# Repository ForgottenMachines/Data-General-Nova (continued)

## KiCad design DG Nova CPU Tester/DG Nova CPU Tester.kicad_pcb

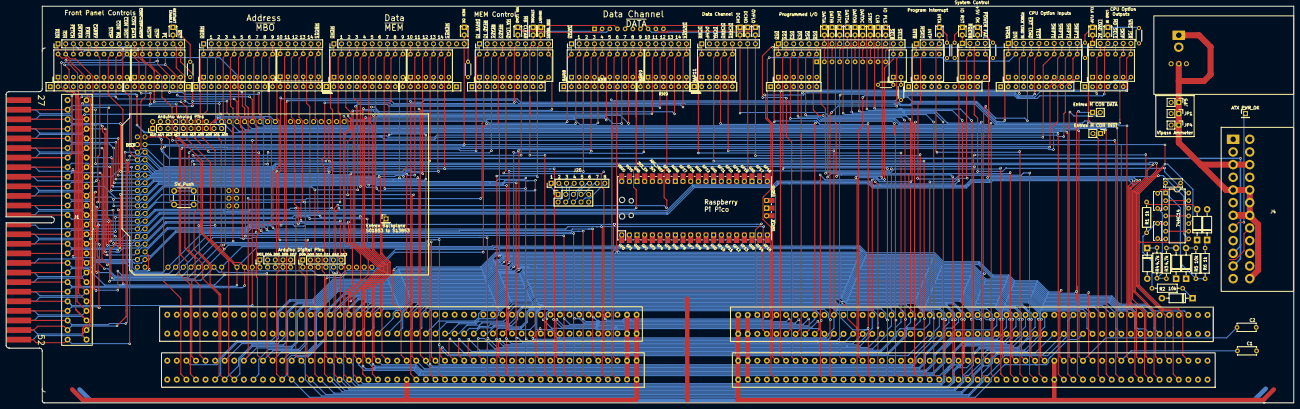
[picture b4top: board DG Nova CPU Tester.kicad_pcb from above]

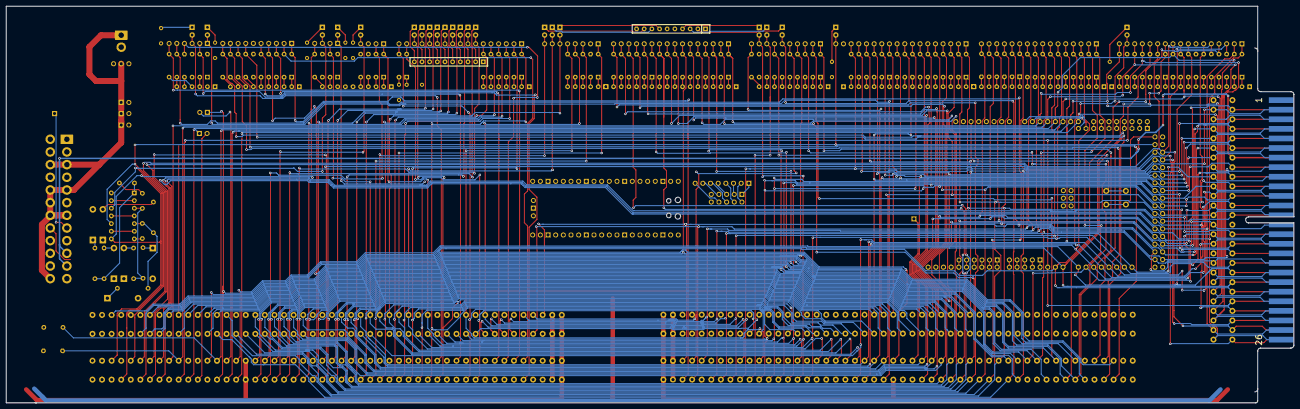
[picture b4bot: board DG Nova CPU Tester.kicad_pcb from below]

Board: 2 copper layers, 426.8 x 131.4 mm, 116 parts (2 on the bottom side), 303 nets.

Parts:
BAR1, BAR3, BAR5, BAR7, BAR8, BAR15: LED Bar 10
BAR2: LED Bar 10; LED Bar 7
BAR4, BAR6, BAR9, BAR10, BAR16: LED Bar 10; LED Bar 6
BAR11: LED Bar 10; LED Bar 5
BAR12: LED Bar 2
BAR13, BAR14: LED Bar 4
C1, C2: CAP_Disc_Common_-_Entrex_Trapezoid; Disc Capacitor Common Entrex Trapezoid
C3, C4, C5: C; C_Disc_D6.0mm_W2.5mm_P5.00mm
D1, D2, D3, D4, D5, D6: 1N4004; D_DO-41_SOD81_P10.16mm_Horizontal
D7, D8, D9, D10, D11, D12, D13, D14, D15, D16, D17, D18, D19, D20, D21, D22, D23, D24, D25, D26, D27, D28: LED; LED_D1.8mm_W3.3mm_H2.4mm
FPIMAGE1: MountingHole; nova frontpanel layout
J1: Front Panel Socket - Backside; DG NOVA Front Pannel Connector - Backside
J2, J3: DG NOVA Backplane Connector - Frontside
J4: ATX-24; Connector_2x12_P4.2mmx5.5mm (ATX Plug)
J5: Front Panel Card Edge; DG Nova Front Panel Card Edge
J6: MBO; PinHeader_1x16_P2.54mm_Vertical
J7: MEM; PinHeader_1x18_P2.54mm_Vertical
J8: Data Channel; PinHeader_1x16_P2.54mm_Vertical
J9: Front Panel Controls; PinHeader_1x17_P2.54mm_Vertical
J10: Programmed I/O; PinHeader_1x17_P2.54mm_Vertical
J11: CPU Option Inputs; PinHeader_1x10_P2.54mm_Vertical
J12: Data Channel; PinHeader_1x08_P2.54mm_Vertical
J13: Program Interrupt; PinHeader_1x04_P2.54mm_Vertical
J14: System Control; PinHeader_1x04_P2.54mm_Vertical
J15, J16: Slot_02x50_Odd_Even; DG NOVA Backplane Connector - Backside
J17: CPU Option Outputs; PinHeader_1x06_P2.54mm_Vertical
J18: MEM Control Outputs; PinHeader_1x10_P2.54mm_Vertical
J19: Logic 8 CH; PinHeader_2x05_P2.54mm_Vertical - Backside
J20: Logic 8 CH; PinHeader_1x08_P2.54mm_Vertical
J21: Arduino Anolog Pins; PinHeader_1x10_P2.54mm_Vertical
J22: Arduino Digital Pins; PinHeader_1x05_P2.54mm_Vertical
J23: Arduino Digital Pins; PinHeader_1x06_P2.54mm_Vertical
JP1, JP4, JP5: Vipass Ammeter; PinHeader_1x02_P2.54mm_Vertical
JP2: Entrex ~{M CON DATA}; PinHeader_1x02_P2.54mm_Vertical
JP3: Entrex ~{M CON INST}; PinHeader_1x02_P2.54mm_Vertical
MES1: XK-001; XK-001_Volt-Amp_Meter - Backside
R1, R6: 1k; R_Axial_DIN0207_L6.3mm_D2.5mm_P10.16mm_Horizontal
R2, R5: 10k; R_Axial_DIN0207_L6.3mm_D2.5mm_P10.16mm_Horizontal
R3, R4: 4.7k; R_Axial_DIN0207_L6.3mm_D2.5mm_P10.16mm_Horizontal
R7, R8, R9, R10, R11, R12, R13, R14, R15: R_US; R_Axial_DIN0204_L3.6mm_D1.6mm_P5.08mm_Horizontal
RN1, RN3, RN5, RN7, RN8, RN11, RN13, RN14, RN15: R_Network09_US; R_Array_SIP10
RN2: R_Network08_US; R_Array_SIP9
RN4, RN6, RN9: R_Network07_US; R_Array_SIP8
RN10, RN16: R_Network05_US; R_Array_SIP6
RN12: R_Network06_US; R_Array_SIP7
SW1: SW_Push; SW_PUSH_6mm
TP1: Entrex Backplane S01B53 to S13B53; PinHeader_1x01_P2.54mm_Vertical
TP2: ATX PWR_OK; PinHeader_1x01_P2.54mm_Vertical
U1: 74HC14; DIP-14_W7.62mm
U2: Pico; RPi_Pico_SMD_TH
XA1: Arduino_Mega2560_Shield

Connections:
+3v3: J4.1 (+3.3V), J4.2 (+3.3V), J4.12 (+3.3V), J4.13 (+3.3V)
+5V: D1.1 (K), D2.2 (A), D3.1 (K), D4.2 (A), D5.1 (K), D6.2 (A), J1.27, J2.3, J2.4, J2.97, J2.98, J3.3, J3.4, J3.97, J3.98, J4.4 (+5V), J4.6 (+5V), J4.21 (+5V), J4.22 (+5V), J4.23 (+5V), J5.27, J15.3, J15.4, J15.97 (Pin_69), J15.98, J16.3, J16.4, J16.97 (Pin_69), J16.98, MES1.1, MES1.3 (PWR), R9.1, R10.1, RN1.1 (common), RN2.1 (common), RN3.1 (common), RN4.1 (common), RN5.1 (common), RN6.1 (common), RN7.1 (common), RN8.1 (common), RN9.1 (common), RN10.1 (common), RN12.1 (common), RN13.1 (common), RN15.1 (common), RN16.1 (common), U1.14 (VCC), U2.39 (VSYS), XA1.5V1 (5V), XA1.5V3 (5V), XA1.5V4 (5V), XA1.VIN
+5V OK: D24.2 (A), J2.8, J14.3, U1.12
+12V Lamp: J1.33, J4.10 (+12V), J4.11 (+12V), J5.33
+VINH: J15.10, J16.84
-5V: J4.20 (-5v), J15.6, J16.81
CLK FLOP: D28.2 (A), J3.48, J17.1
CLR: D20.2 (A), J2.50, J10.14, J15.50
DATIA: D12.2 (A), J2.44, J10.7, J15.44
DATIB: D16.2 (A), J2.42, J10.8, J15.42
DATIC: D17.2 (A), J2.54, J10.9, J15.54
DATOA: D21.2 (A), J2.58, J10.10, J15.58
DATOB: D22.2 (A), J2.56, J10.11, J15.56
DATOC: D18.2 (A), J2.48, J10.12, J15.48
DCHI: D13.2 (A), J3.37, J12.6, J16.37
DCHO: D14.2 (A), J3.33, J12.7, J16.33
Entrex Backplane S01B53 to S13B53: J3.53, TP1.1
Entrex P10.19: J2.24, JP3.2 (B)
Entrex P10.30: J2.29, JP2.2 (B)
GND: C1.1, C2.1, C3.2, C4.2, C5.2, J1.1, J1.40, J2.1, J2.2, J2.33, J2.34, J2.99, J2.100, J3.1, J3.2, J3.50, J3.99, J3.100, J5.1, J5.40, J15.1, J15.2, J15.33, J15.34, J15.99, J15.100, J16.1, J16.2, J16.50, J16.89, J16.92, J16.99, J16.100, J19.10, JP1.2 (B), JP4.2 (B), JP5.2 (B), MES1.5, R7.1, R8.1, R11.1, R12.1, R13.1, R14.1, R15.1, RN11.1 (common), RN14.1 (common), SW1.1, U1.7 (GND), U2.3 (GND), U2.8 (GND), U2.13 (GND), U2.18 (GND), U2.23 (GND), U2.28 (GND), U2.33 (AGND), U2.38 (GND), U2.42 (GND), XA1.GND1 (GND), XA1.GND2 (GND), XA1.GND3 (GND), XA1.GND5 (GND), XA1.GND6 (GND)
GND After Meter: J4.3 (GND), J4.5 (GND), J4.7 (GND), J4.15 (GND), J4.17 (GND), J4.18 (GND), J4.19 (GND), J4.24 (GND), JP1.1 (A), JP4.1 (A), JP5.1 (A), MES1.2, MES1.4
INH GND: J15.8, J15.14, J15.16, J15.20, J15.22, J15.26, J15.30, J15.31
INHIBIT: D11.2 (A), J3.30, J16.30, J18.9
INTA: D25.2 (A), J2.40, J13.4, J15.40
IO PLS: D23.2 (A), J2.74, J10.15, J15.74
IO RST: D26.2 (A), J2.70, J14.1, J15.70
LOAD IR: D27.2 (A), J2.73, J17.3
Logic1: J19.1, J20.1
Logic2: J19.2, J20.2
Logic3: J19.3, J20.3
Logic4: J19.4, J20.4
Logic5: J19.5, J20.5
Logic6: J19.6, J20.6
Logic7: J19.7, J20.7
Logic8: J19.8, J20.8
MB LOAD: D9.2 (A), J3.74, J16.74, J18.6
MEM OK: D8.2 (A), J2.9, J7.18, U1.10, XA1.D52
unnamed: BAR12.1, R10.2
unnamed: BAR12.2, R9.2
unnamed: C3.1, R1.2, R2.1, U1.5
unnamed: C4.1, R3.2, R4.1, U1.3
unnamed: C5.1, R5.2, R6.1, U1.1
unnamed: D1.2 (A), R1.1
unnamed: D2.1 (K), R2.2
unnamed: D3.2 (A), R3.1
unnamed: D4.1 (K), R4.2
unnamed: D5.2 (A), R5.1
unnamed: D6.1 (K), R6.2
unnamed: D7.1 (K), R7.2
unnamed: D8.1 (K), R8.2
unnamed: D9.1 (K), RN11.2 (R1)
unnamed: D10.1 (K), RN11.3 (R2)
unnamed: D11.1 (K), RN11.4 (R3)
unnamed: D12.1 (K), RN14.2 (R1)
unnamed: D13.1 (K), RN11.7 (R6)
unnamed: D14.1 (K), RN11.8 (R7)
unnamed: D15.1 (K), RN11.9 (R8)
unnamed: D16.1 (K), RN14.3 (R2)
unnamed: D17.1 (K), RN14.4 (R3)
unnamed: D18.1 (K), RN14.7 (R6)
unnamed: D19.1 (K), RN14.8 (R7)
unnamed: D20.1 (K), RN14.9 (R8)
unnamed: D21.1 (K), RN14.5 (R4)
unnamed: D22.1 (K), RN14.6 (R5)
unnamed: D23.1 (K), RN14.10 (R9)
unnamed: D24.1 (K), R14.2
unnamed: D25.1 (K), R11.2
unnamed: D26.1 (K), R12.2
unnamed: D27.1 (K), R13.2
unnamed: D28.1 (K), R15.2
unnamed: J21.1, XA1.A15
unnamed: J21.2, XA1.A14
unnamed: J21.3, XA1.A13
unnamed: J21.4, XA1.A12
unnamed: J21.5, XA1.A11
unnamed: J21.6, XA1.A10
unnamed: J21.7, XA1.A9
unnamed: J21.8, XA1.A8
unnamed: J21.9, XA1.A1
unnamed: J21.10, XA1.A0
unnamed: J22.1, XA1.D3 (D3_INT1)
unnamed: J22.2, XA1.D4
unnamed: J22.3, XA1.D5
unnamed: J22.4, XA1.D6
unnamed: J22.5, XA1.D7
unnamed: J23.1, XA1.D8
unnamed: J23.2, XA1.D9
unnamed: J23.3, XA1.D10
unnamed: J23.4, XA1.D11
unnamed: J23.5, XA1.D12
unnamed: J23.6, XA1.D13
unnamed: BAR1.1, RN1.2 (R1)
unnamed: BAR1.2, RN1.3 (R2)
unnamed: BAR1.3, RN1.4 (R3)
unnamed: BAR1.4, RN1.5 (R4)
unnamed: BAR1.5, RN1.6 (R5)
unnamed: BAR1.6, RN1.7 (R6)
unnamed: BAR1.7, RN1.8 (R7)
unnamed: BAR1.8, RN1.9 (R8)
unnamed: BAR1.9, RN1.10 (R9)
unnamed: BAR2.7, RN2.2 (R1)
unnamed: BAR2.6, RN2.3 (R2)
unnamed: BAR2.5, RN2.4 (R3)
unnamed: BAR2.4, RN2.5 (R4)
unnamed: BAR2.3, RN2.6 (R5)
unnamed: BAR2.2, RN2.7 (R6)
unnamed: BAR2.1, RN2.8 (R7)
unnamed: BAR1.10, RN2.9 (R8)
unnamed: BAR3.1, RN3.2 (R1)
unnamed: BAR3.2, RN3.3 (R2)
unnamed: BAR3.3, RN3.4 (R3)
unnamed: BAR3.4, RN3.5 (R4)
unnamed: BAR3.5, RN3.6 (R5)
unnamed: BAR3.6, RN3.7 (R6)
unnamed: BAR3.7, RN3.8 (R7)
unnamed: BAR3.8, RN3.9 (R8)
unnamed: BAR3.9, RN3.10 (R9)
unnamed: BAR4.6, RN4.2 (R1)
unnamed: BAR4.5, RN4.3 (R2)
unnamed: BAR4.4, RN4.4 (R3)
unnamed: BAR4.3, RN4.5 (R4)
unnamed: BAR4.2, RN4.6 (R5)
unnamed: BAR4.1, RN4.7 (R6)
unnamed: BAR3.10, RN4.8 (R7)
unnamed: BAR5.1, RN5.2 (R1)
unnamed: BAR5.2, RN5.3 (R2)
unnamed: BAR5.3, RN5.4 (R3)
unnamed: BAR5.4, RN5.5 (R4)
unnamed: BAR5.5, RN5.6 (R5)
unnamed: BAR5.6, RN5.7 (R6)
unnamed: BAR5.7, RN5.8 (R7)
unnamed: BAR5.8, RN5.9 (R8)
unnamed: BAR5.9, RN5.10 (R9)
unnamed: BAR6.6, RN6.2 (R1)
unnamed: BAR6.5, RN6.3 (R2)
unnamed: BAR6.4, RN6.4 (R3)
unnamed: BAR6.3, RN6.5 (R4)
unnamed: BAR6.2, RN6.6 (R5)
unnamed: BAR6.1, RN6.7 (R6)
unnamed: BAR5.10, RN6.8 (R7)
unnamed: BAR7.1, RN7.2 (R1)
unnamed: BAR7.2, RN7.3 (R2)
unnamed: BAR7.3, RN7.4 (R3)
unnamed: BAR7.4, RN7.5 (R4)
unnamed: BAR7.5, RN7.6 (R5)
unnamed: BAR7.6, RN7.7 (R6)
unnamed: BAR7.7, RN7.8 (R7)
unnamed: BAR7.8, RN7.9 (R8)
unnamed: BAR7.10, RN7.10 (R9)
unnamed: BAR8.1, RN8.2 (R1)
unnamed: BAR8.2, RN8.3 (R2)
unnamed: BAR8.3, RN8.4 (R3)
unnamed: BAR8.4, RN8.5 (R4)
unnamed: BAR8.5, RN8.6 (R5)
unnamed: BAR8.6, RN8.7 (R6)
unnamed: BAR8.7, RN8.8 (R7)
unnamed: BAR8.8, RN8.9 (R8)
unnamed: BAR8.9, RN8.10 (R9)
unnamed: BAR9.6, RN9.2 (R1)
unnamed: BAR9.5, RN9.3 (R2)
unnamed: BAR9.4, RN9.4 (R3)
unnamed: BAR9.3, RN9.5 (R4)
unnamed: BAR9.2, RN9.6 (R5)
unnamed: BAR9.1, RN9.7 (R6)
unnamed: BAR8.10, RN9.8 (R7)
unnamed: BAR11.1, RN10.2 (R1)
unnamed: BAR11.2, RN10.3 (R2)
unnamed: BAR11.3, RN10.4 (R3)
unnamed: BAR11.4, RN10.5 (R4)
unnamed: BAR11.5, RN10.6 (R5)
unnamed: BAR10.1, RN12.2 (R1)
unnamed: BAR10.2, RN12.3 (R2)
unnamed: BAR10.3, RN12.4 (R3)
unnamed: BAR10.4, RN12.5 (R4)
unnamed: BAR10.5, RN12.6 (R5)
unnamed: BAR10.6, RN12.7 (R6)
unnamed: BAR13.1, RN13.2 (R1)
unnamed: BAR13.2, RN13.3 (R2)
unnamed: BAR13.3, RN13.4 (R3)
unnamed: BAR13.4, RN13.5 (R4)
unnamed: BAR14.2, RN13.9 (R8)
unnamed: BAR14.4, RN13.10 (R9)
unnamed: BAR15.1, RN15.2 (R1)
unnamed: BAR15.2, RN15.3 (R2)
unnamed: BAR15.3, RN15.4 (R3)
unnamed: BAR15.4, RN15.5 (R4)
unnamed: BAR15.5, RN15.6 (R5)
unnamed: BAR15.7, RN15.7 (R6)
unnamed: BAR15.8, RN15.8 (R7)
unnamed: BAR15.9, RN15.9 (R8)
unnamed: BAR15.10, RN15.10 (R9)
unnamed: BAR16.2, RN16.3 (R2)
unnamed: BAR16.6, RN16.4 (R3)
unnamed: BAR16.4, RN16.5 (R4)
unnamed: BAR16.5, RN16.6 (R5)
unnamed: U1.6, U1.9
unnamed: U1.4, U1.11
unnamed: U1.2, U1.13
unnamed: SW1.2, XA1.RST1 (RESET)
OVFLO: D15.2 (A), J3.39, J12.8, J16.39
PWR_OK: J4.8 (PWR_OK), TP2.1
RESTART ENABLE: D7.2 (A), J1.19, J2.32, J5.19, J9.16, XA1.A7
STROBE: D10.2 (A), J3.20, J16.20, J18.8
STRT: D19.2 (A), J2.52, J10.13, J15.52
~CARRY: BAR1.15 (K), J1.49, J2.15, J5.49, J9.6, XA1.D32
~CON DATA: BAR2.20 (K), J1.46, J2.28, J5.46, J9.11, JP2.1 (A), XA1.D0 (D0_RX0)
~CON INST: BAR1.11 (K), J1.22, J2.22, J5.22, J9.10, JP3.1 (A), XA1.A4
~CON RQ: BAR1.12 (K), C2.2, J1.21, J2.27, J5.21, J9.9, XA1.A5
~CONT+ISTP+MSTP: BAR2.19 (K), J1.47, J2.25, J5.47, J9.12, XA1.D1 (D1_TX0)
~DATA0: BAR8.20 (K), J3.62, J8.1, J16.62
~DATA1: BAR8.19 (K), J3.65, J8.2, J16.65
~DATA2: BAR8.18 (K), J3.82, J8.3, J16.82
~DATA3: BAR8.17 (K), J3.73, J8.4, J16.73
~DATA4: BAR8.16 (K), J3.61, J8.5, J16.61
~DATA5: BAR8.15 (K), J3.57, J8.6, J16.57
~DATA6: BAR8.14 (K), J3.95, J8.7, J16.95
~DATA7: BAR8.13 (K), J3.55, J8.8, J16.55
~DATA8: BAR8.12 (K), J3.60, J8.9, J16.60
~DATA9: BAR8.11 (K), J3.63, J8.10, J16.63
~DATA10: BAR9.20 (K), J3.75, J8.11, J16.75
~DATA11: BAR9.19 (K), J3.58, J8.12, J16.58
~DATA12: BAR9.18 (K), J3.59, J8.13, J16.59
~DATA13: BAR9.17 (K), J3.64, J8.14, J16.64
~DATA14: BAR9.16 (K), J3.56, J8.15, J16.56
~DATA15: BAR9.15 (K), J3.66, J8.16, J16.66
~DCHA: BAR11.18 (K), J2.60, J12.3, J15.60
~DCHM0: BAR11.17 (K), J3.17, J12.4, J16.17
~DCHM1: BAR11.16 (K), J3.21, J12.5, J16.21
~DCHR: BAR11.20 (K), J3.35, J12.1, J16.35
~DEFER: BAR1.17 (K), J1.52, J2.12, J5.52, J9.4, XA1.D50
~DIV: BAR15.19 (K), J2.91, J11.2
~DRIVE IO: BAR7.20 (K), J3.88, J16.88, J18.1
~DS0: BAR10.20 (K), J2.72, J10.1, J15.72
~DS1: BAR10.19 (K), J2.68, J10.2, J15.68
~DS2: BAR10.18 (K), J2.66, J10.3, J15.66
~DS3: BAR10.17 (K), J2.46, J10.4, J15.46
~DS4: BAR10.16 (K), J2.62, J10.5, J15.62
~DS5: BAR10.15 (K), J2.64, J10.6, J15.64
~EXEC: BAR1.16 (K), J1.51, J2.11, J5.51, J9.5, XA1.D51
~EXT LOAD: BAR15.17 (K), J2.47, J3.49, J11.4
~FETCH: BAR1.18 (K), J1.50, J2.13, J2.49, J5.50, J9.3, XA1.D49
~FORCE LOAD IR: BAR15.18 (K), J2.85, J11.3
~INH TRANS: BAR7.11 (K), J3.45, J16.45, J18.10
~INTR: BAR13.20 (K), J3.29, J13.1, J16.29
~ION: BAR1.19 (K), J1.25, J2.16, J5.25, J9.2, XA1.D31
~ISTP: BAR2.17 (K), J1.24, J2.17, J5.24, J9.14, XA1.A2
~LOAD AC: BAR16.19 (K), J2.77, J17.2
~MA LOAD: BAR7.16 (K), J3.7, J16.7, J18.5
~MB CLEAR: BAR7.14 (K), J3.86, J16.86, J18.7
~MBO0: BAR3.20 (K), J3.79, J6.1, J16.79
~MBO1: BAR3.19 (K), J1.14, J3.77, J5.14, J6.2, J16.77, XA1.D15 (D15_RX3)
~MBO2: BAR3.18 (K), J1.15, J3.44, J5.15, J6.3, J16.44, XA1.D16 (D16_TX2)
~MBO3: BAR3.17 (K), J1.38, J3.43, J5.38, J6.4, J16.43, XA1.D17 (D17_RX2)
~MBO4: BAR3.16 (K), J1.16, J3.42, J5.16, J6.5, J16.42, XA1.D18 (D18_TX1)
~MBO5: BAR3.15 (K), J1.11, J3.32, J5.11, J6.6, J16.32, XA1.D19 (D19_RX1)
~MBO6: BAR3.14 (K), J1.35, J3.16, J5.35, J6.7, J16.16, XA1.D20 (D20_SDA)
~MBO7: BAR3.13 (K), J1.9, J3.14, J5.9, J6.8, J16.14, XA1.D21 (D21_SCL)
~MBO8: BAR3.12 (K), J1.18, J3.12, J5.18, J6.9, J16.12, XA1.D22
~MBO9: BAR3.11 (K), J1.8, J3.9, J5.8, J6.10, J16.9, XA1.D23
~MBO10: BAR4.20 (K), J1.44, J3.8, J5.44, J6.11, J16.8, XA1.D24
~MBO11: BAR4.19 (K), J1.6, J3.5, J5.6, J6.12, J16.5, XA1.D25
~MBO12: BAR4.18 (K), J1.30, J2.39, J5.30, J6.13, J15.39, XA1.D26
~MBO13: BAR4.17 (K), J1.4, J2.37, J5.4, J6.14, J15.37, XA1.D27
~MBO14: BAR4.16 (K), J1.12, J2.43, J5.12, J6.15, J15.43, XA1.D28
~MBO15: BAR4.15 (K), J1.28, J2.41, J5.28, J6.16, J15.41, XA1.D29
~MD SEL1: BAR16.17 (K), J2.87, J17.4
~MEM0: BAR5.20 (K), J1.39, J3.71, J5.39, J7.1, J16.71, XA1.D33
~MEM1: BAR5.19 (K), J1.41, J3.70, J5.41, J7.2, J16.70, XA1.D34
~MEM2: BAR5.18 (K), J1.13, J3.47, J5.13, J7.3, J16.47, XA1.D35
~MEM3: BAR5.17 (K), J1.43, J3.68, J5.43, J7.4, J16.68, XA1.D36
~MEM4: BAR5.16 (K), J1.37, J3.28, J5.37, J7.5, J16.28, XA1.D37
~MEM5: BAR5.15 (K), J1.36, J3.26, J5.36, J7.6, J16.26, XA1.D38
~MEM6: BAR5.14 (K), J1.10, J3.22, J5.10, J7.7, J16.22, XA1.D39
~MEM7: BAR5.13 (K), J1.42, J3.24, J5.42, J7.8, J16.24, XA1.D40
~MEM8: BAR5.12 (K), J1.34, J2.55, J5.34, J7.9, J15.55, XA1.D41
~MEM9: BAR5.11 (K), J1.7, J2.53, J5.7, J7.10, J15.53, XA1.D42
~MEM10: BAR6.20 (K), J1.32, J2.45, J5.32, J7.11, J15.45, XA1.D43
~MEM11: BAR6.19 (K), J1.31, J2.51, J5.31, J7.12, J15.51, XA1.D44
~MEM12: BAR6.18 (K), J1.5, J2.36, J5.5, J7.13, J15.36, XA1.D45
~MEM13: BAR6.17 (K), J1.29, J2.35, J5.29, J7.14, J15.35, XA1.D46
~MEM14: BAR6.16 (K), J1.3, J3.76, J5.3, J7.15, J16.76, XA1.D47
~MEM15: BAR6.15 (K), J1.2, J3.18, J5.2, J7.16, J16.18, XA1.D48
~MSKO: BAR13.19 (K), J2.38, J13.2, J15.38
~MSTP: BAR2.18 (K), J1.48, J2.20, J5.48, J9.13, XA1.D2 (D2_INT0)
~PL: BAR2.16 (K), C1.2, J1.23, J2.19, J5.23, J9.15, XA1.A3
~POWER FAIL: BAR14.17 (K), J2.5, J14.4, U1.8
~READ1: BAR7.18 (K), J3.87, J16.87, J18.3
~READ2: BAR7.17 (K), J3.90, J16.90, J18.4
~READ IO: BAR7.19 (K), J3.83, J16.83, J18.2
~RQENB: BAR14.19 (K), J3.41, J14.2, J16.41
~RST: BAR2.14 (K), J1.20, J2.30, J5.20, J9.17, XA1.A6
~RUN: BAR1.20 (K), J1.26, J2.14, J5.26, J9.1, XA1.D30
~SELB: BAR12.20 (K), J2.82, J10.16, J15.82
~SELD: BAR12.19 (K), J2.80, J10.17, J15.80
~SHIFT0: BAR15.14 (K), J3.94, J11.7
~SHIFT1: BAR15.13 (K), J3.96, J11.8
~SHIFT2: BAR15.12 (K), J3.93, J11.9
~SHIFT3: BAR15.11 (K), J3.91, J11.10
~SKIP: BAR16.16 (K), J3.69, J17.5
~STOP: BAR1.13 (K), J1.45, J2.31, J5.45, J9.8, XA1.D14 (D14_TX3)
~TEST: BAR15.16 (K), J2.92, J11.5
~WAS JSR: BAR16.15 (K), J2.89, J17.6
~WHOA: BAR15.20 (K), J3.6, J11.1

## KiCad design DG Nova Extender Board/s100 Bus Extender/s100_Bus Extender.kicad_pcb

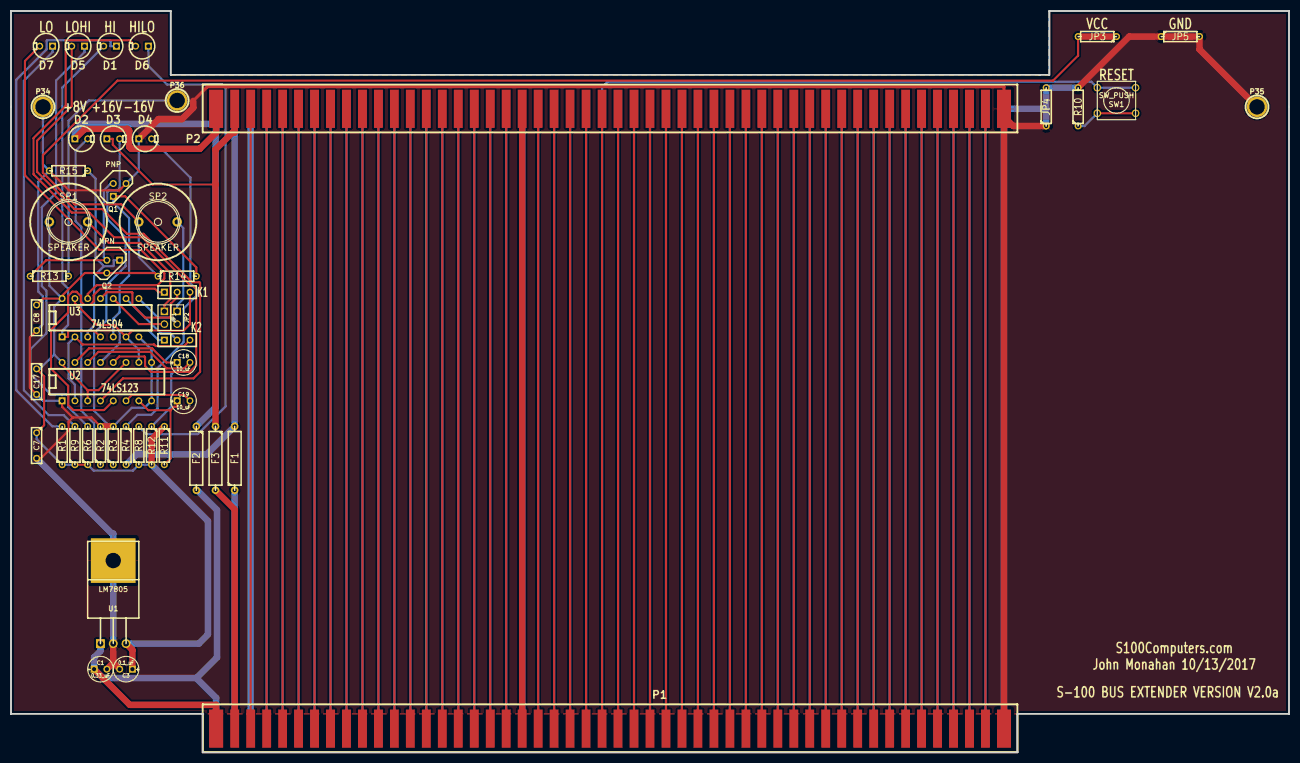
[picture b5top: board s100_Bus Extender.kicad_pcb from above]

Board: 2 copper layers, 254.0 x 147.3 mm, 50 parts (0 on the bottom side), 132 nets.

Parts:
C1: 0.33_uF; C1V5
C3: 0.1_uF; C1V5
C7, C8, C17: 0.1_uF; C2
C18, C19: 10_uF; C1V5
D1, D2, D3, D4, D5, D6, D7: LED; LEDV
F1, F2, F3: FUSE; R5
JP1, JP2: JUMPER; PIN_ARRAY_2X1
JP3, JP4, JP5: JUMPER; R3
K1, K2: CONN_3; SIL-3
P1, P2: S100_MALE
P34, P35, P36: CONN_1; 1pin
Q1: PNP; TO92-INVERT
Q2: NPN; TO92
R1, R6, R8, R9: 180; R3
R2: 4700; R3
R3, R4: 20K; R3
R10: 10; R3
R11, R12: 470; R3
R13: 1K; R3
R14: 6800; R3
R15: 390; R3
SP1, SP2: SPEAKER; BUZZER_AL11P_modified
SW1: SW_PUSH; SW_PUSH_SMALL
U1: LM7805; TO220
U2: 74LS123; 16dip300
U3: 74LS04; 14dip300

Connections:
/0V_A: P1.20, P2.20
/0V_B: P1.53, P2.53
/0V_C: P1.70, P2.70
/+8V: C1.1, F2.2, P1.1, P1.51, U1.VI
/+16V: F3.2, P1.2
/-16V: F1.1, P1.52
/A0: P1.79, P2.79
/A1: P1.80, P2.80
/A2: P1.81, P2.81
/A3: P1.31, P2.31
/A4: P1.30, P2.30
/A5: P1.29, P2.29
/A6: P1.82, P2.82
/A7: P1.83, P2.83
/A8-: P1.84, P2.84
/A9-: P1.34, P2.34
/A10-: P1.37, P2.37
/A11-: P1.87, P2.87
/A12-: P1.33, P2.33
/A13-: P1.85, P2.85
/A14-: P1.86, P2.86
/A15-: P1.32, P2.32
/A16: P1.16, P2.16
/A17: P1.17, P2.17
/A18: P1.15, P2.15
/A19: P1.59, P2.59
/A20: P1.61, P2.61
/A21: P1.62, P2.62
/A22: P1.63, P2.63
/A23: P1.64, P2.64
/ADSB*: P1.22, P2.22
/CDSB*: P1.19, P2.19
/CLOCK: P1.49, P2.49
/DI0: P1.95, P2.95
/DI1: P1.94, P2.94
/DI2: P1.41, P2.41
/DI3: P1.42, P2.42
/DI4: P1.91, P2.91
/DI5: P1.92, P2.92
/DI6: P1.93, P2.93
/DI7: P1.43, P2.43
/DO0: P1.36, P2.36
/DO1: P1.35, P2.35
/DO2: P1.88, P2.88
/DO3: P1.89, P2.89
/DO4: P1.38, P2.38
/DO5: P1.39, P2.39
/DO6: P1.40, P2.40
/DO7: P1.90, P2.90
/DODSB*: P1.23, P2.23
/ERROR*: P1.98, P2.98
/F+8V: D2.1, F2.1, P2.1, P2.51
/F+16V: D3.1, F3.1, P2.2
/F-16V: F1.2, P2.52, R4.2
/HOLD*: P1.74, P2.74
/INT*: P1.73, P2.73
/MWRT: P1.68, P2.68
/NDEF1: P1.21, P2.21
/NDEF2: P1.65, P2.65
/NDEF3: P1.66, P2.66
/NMI*: P1.12, P2.12
/PHANTOM*: P1.67, P2.67
/PHI: P1.24, P2.24
/POC*: P1.99, P2.99
/PWRFAIL*: P1.13, P2.13
/RDY: P1.72, P2.72
/RESET*: P1.75, P2.75, SW1.2
/RFU1: P1.27, P2.27
/RFU2: P1.28, P2.28
/RFU3: P1.69, P2.69
/RFU4: P1.71, P2.71
/SDSB*: P1.18, P2.18
/SIXTN*: P1.60, P2.60
/SLAVE_CLR*: P1.54, P2.54
/TMA0*: P1.55, P2.55
/TMA1*: P1.56, P2.56
/TMA2*: P1.57, P2.57
/TMA3*: P1.14, P2.14
/VI0*: P1.4, P2.4
/VI1*: P1.5, P2.5
/VI2*: P1.6, P2.6
/VI3*: P1.7, P2.7
/VI4*: P1.8, P2.8
/VI5*: P1.9, P2.9
/VI6*: P1.10, P2.10
/VI7*: P1.11, P2.11
/XRDY: P1.3, P2.3
/pDBIN: P1.78, P2.78
/pHLDA: P1.26, P2.26
/pSTVAL*: P1.25, P2.25
/pSYNC: P1.76, P2.76
/pWR*: P1.77, P2.77
/sHLTA: P1.48, P2.48
/sINP: P1.46, P2.46
/sINTA: P1.96, P2.96
/sM1: P1.44, P2.44
/sMEMR: P1.47, P2.47
/sOUT: P1.45, P2.45
/sWO*: P1.97, P2.97
/sXTRQ*: P1.58, P2.58
GND: C1.2, C3.2, C7.2, C8.2, C17.2, D4.1, JP4.1, JP4.2, JP5.1, JP5.2, P1.50, P1.100, P2.50, P2.100, P34.1, P35.1, Q1.3, R2.2, R3.2, R10.2, R15.2, U1.GND, U2.1, U2.8, U2.9, U3.7
unnamed: K1.2, U3.11
unnamed: K2.1, U2.13
unnamed: K2.2, U3.9
unnamed: K2.3, U2.2, U3.2
unnamed: JP2.2, U3.8
unnamed: D1.2, U3.1, U3.4
unnamed: Q1.1, R14.2, U3.5
unnamed: Q2.1, R15.1, U3.3
unnamed: K1.3, U2.10, U3.6, U3.13
unnamed: K1.1, U2.5
unnamed: C19.2, U2.6
unnamed: C19.1, R11.2, U2.7
unnamed: D6.2, U2.12
unnamed: D6.1, R8.2
unnamed: D5.1, R6.2
unnamed: D5.2, U2.4
unnamed: D4.2, R4.1
unnamed: D3.2, R3.1
unnamed: D2.2, R2.1
unnamed: D7.1, R9.2
unnamed: D7.2, U3.12
unnamed: JP2.1, SP2.2
unnamed: D1.1, R1.2
unnamed: C18.1, R12.1, U2.15
unnamed: C18.2, U2.14
unnamed: JP1.1, SP1.2
unnamed: JP1.2, U3.10
unnamed: P36.1, R13.2
unnamed: Q1.2, Q2.2, R13.1
unnamed: R10.1, SW1.1
VCC: C3.1, C7.1, C8.1, C17.1, JP3.1, JP3.2, Q2.3, R1.1, R6.1, R8.1, R9.1, R11.1, R12.2, R14.1, SP1.1, SP2.1, U1.VO, U2.3, U2.11, U2.16, U3.14

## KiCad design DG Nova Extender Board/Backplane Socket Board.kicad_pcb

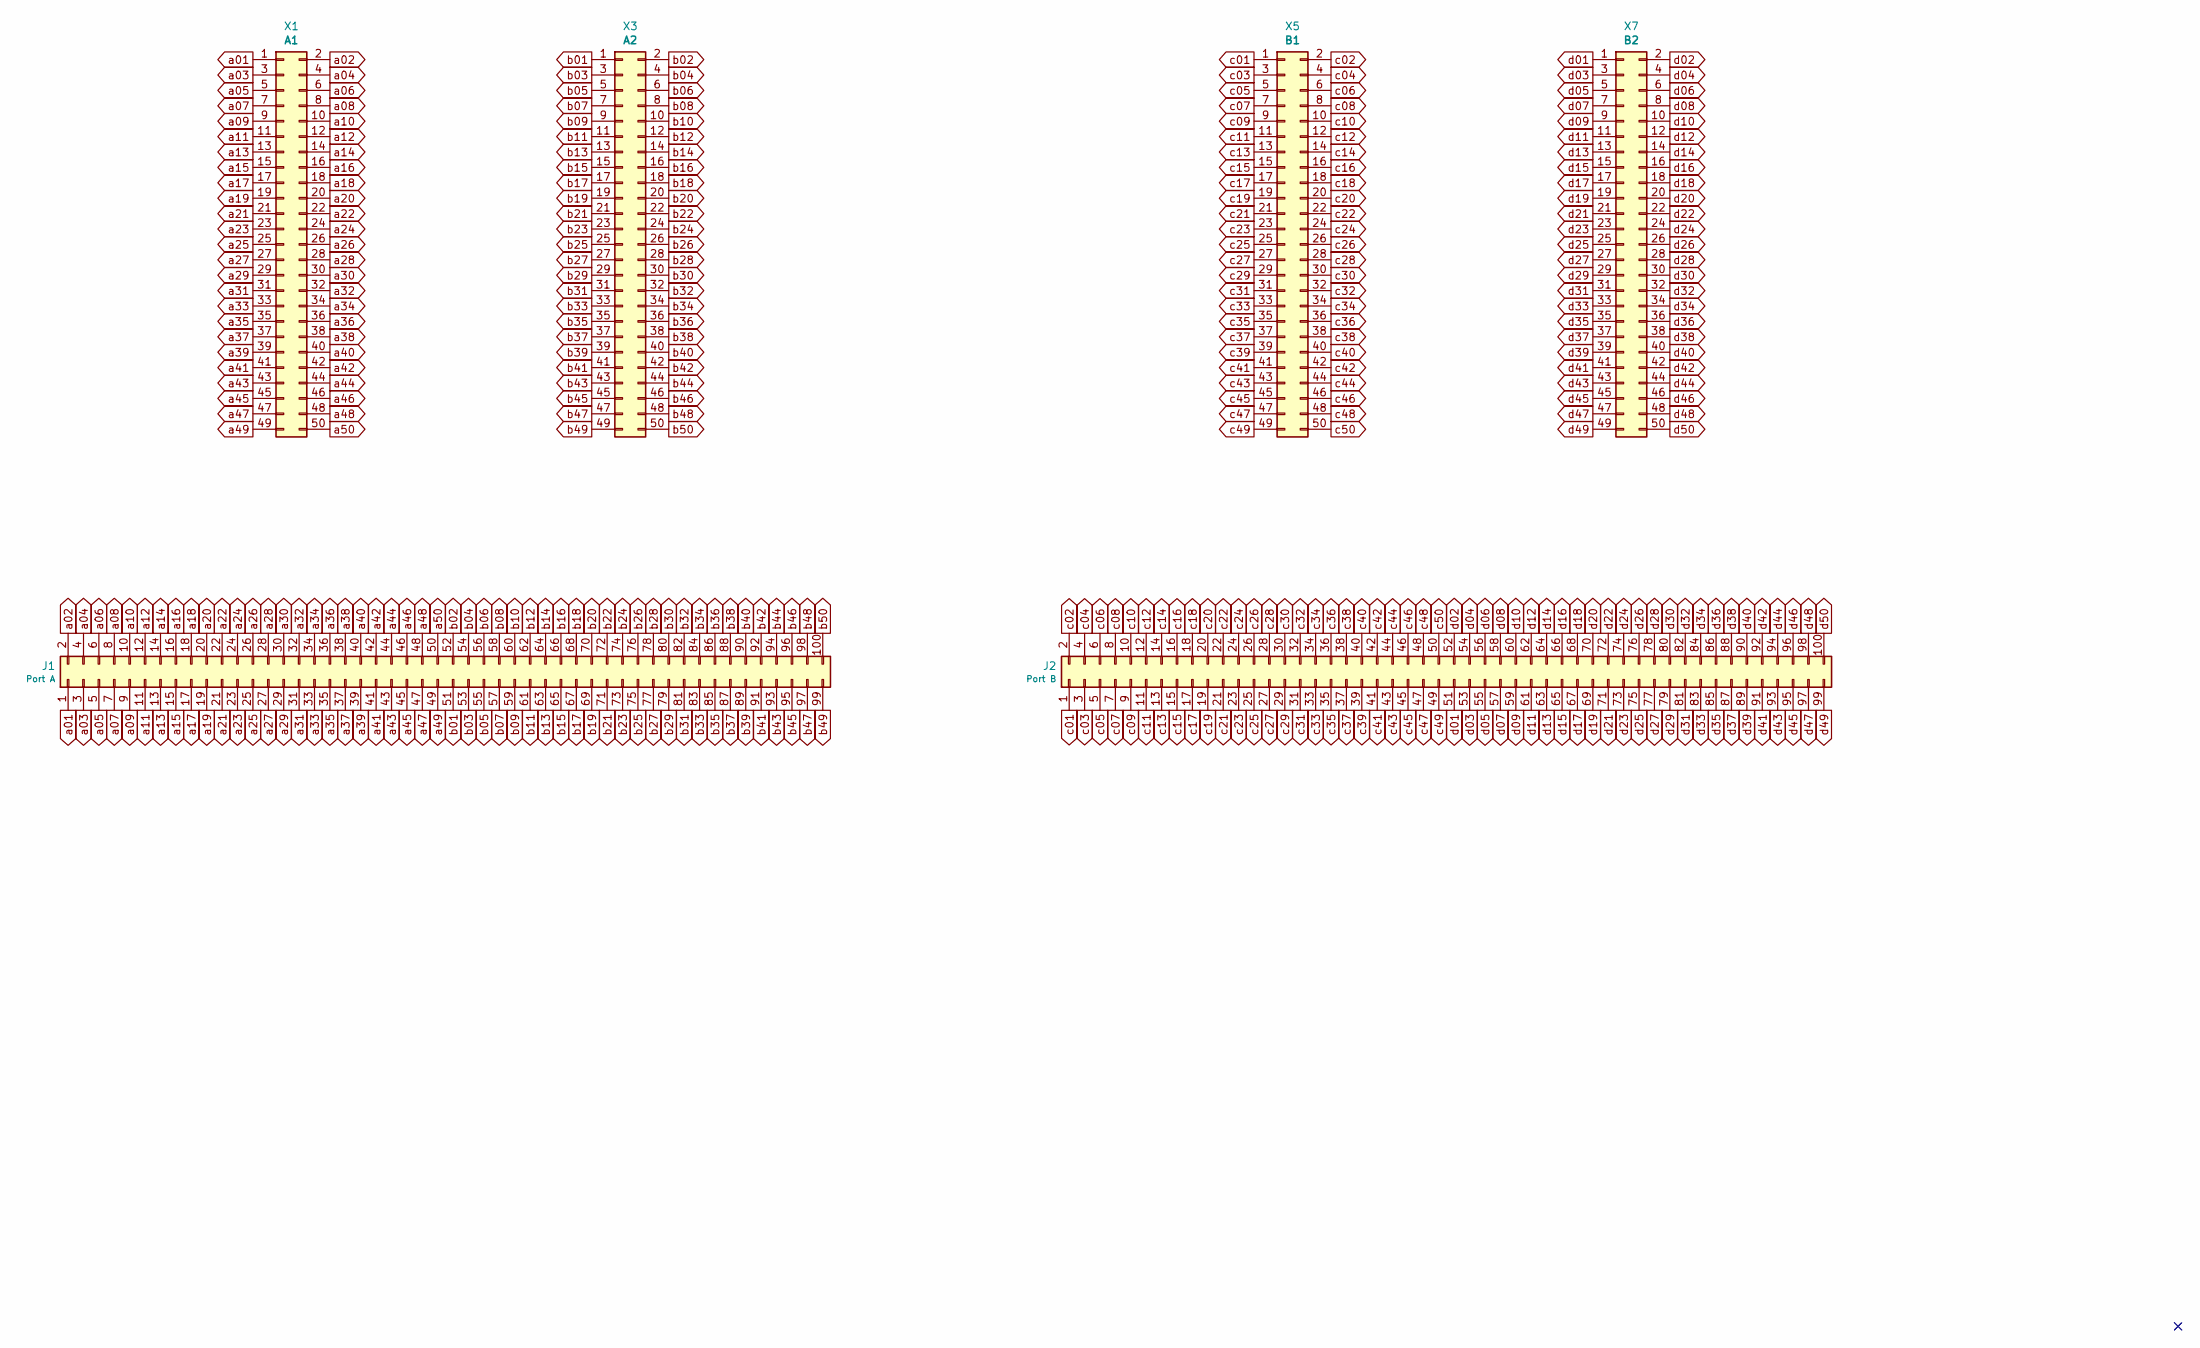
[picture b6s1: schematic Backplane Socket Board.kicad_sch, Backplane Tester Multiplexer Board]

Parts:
J1: Port A; DG NOVA Backplane Connector - Frontside
J2: Port B; DG NOVA Backplane Connector - Frontside
X1: A1; IDC-Header_2x25_P2.54mm - Backside; Part-Number SBH11-PBPC-D25-ST-BK; Digi-Key S9176-ND
X3: A2; IDC-Header_2x25_P2.54mm - Backside; Part-Number SBH11-PBPC-D25-ST-BK; Digi-Key S9176-ND
X5: B1; IDC-Header_2x25_P2.54mm - Backside; Part-Number SBH11-PBPC-D25-ST-BK; Digi-Key S9176-ND
X7: B2; IDC-Header_2x25_P2.54mm - Backside; Part-Number SBH11-PBPC-D25-ST-BK; Digi-Key S9176-ND

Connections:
a01: J1.1, X1.1
a02: J1.2, X1.2
a03: J1.3, X1.3
a04: J1.4, X1.4
a05: J1.5, X1.5
a06: J1.6, X1.6
a07: J1.7, X1.7
a08: J1.8, X1.8
a09: J1.9, X1.9
a10: J1.10, X1.10
a11: J1.11, X1.11
a12: J1.12, X1.12
a13: J1.13, X1.13
a14: J1.14, X1.14
a15: J1.15, X1.15
a16: J1.16, X1.16
a17: J1.17, X1.17
a18: J1.18, X1.18
a19: J1.19, X1.19
a20: J1.20, X1.20
a21: J1.21, X1.21
a22: J1.22, X1.22
a23: J1.23, X1.23
a24: J1.24, X1.24
a25: J1.25, X1.25
a26: J1.26, X1.26
a27: J1.27, X1.27
a28: J1.28, X1.28
a29: J1.29, X1.29
a30: J1.30, X1.30
a31: J1.31, X1.31
a32: J1.32, X1.32
a33: J1.33, X1.33
a34: J1.34, X1.34
a35: J1.35, X1.35
a36: J1.36, X1.36
a37: J1.37, X1.37
a38: J1.38, X1.38
a39: J1.39, X1.39
a40: J1.40, X1.40
a41: J1.41, X1.41
a42: J1.42, X1.42
a43: J1.43, X1.43
a44: J1.44, X1.44
a45: J1.45, X1.45
a46: J1.46, X1.46
a47: J1.47, X1.47
a48: J1.48, X1.48
a49: J1.49, X1.49
a50: J1.50, X1.50
b01: J1.51, X3.1
b02: J1.52, X3.2
b03: J1.53, X3.3
b04: J1.54, X3.4
b05: J1.55, X3.5
b06: J1.56, X3.6
b07: J1.57, X3.7
b08: J1.58, X3.8
b09: J1.59, X3.9
b10: J1.60, X3.10
b11: J1.61, X3.11
b12: J1.62, X3.12
b13: J1.63, X3.13
b14: J1.64, X3.14
b15: J1.65, X3.15
b16: J1.66, X3.16
b17: J1.67, X3.17
b18: J1.68, X3.18
b19: J1.69, X3.19
b20: J1.70, X3.20
b21: J1.71, X3.21
b22: J1.72, X3.22
b23: J1.73, X3.23
b24: J1.74, X3.24
b25: J1.75, X3.25
b26: J1.76, X3.26
b27: J1.77, X3.27
b28: J1.78, X3.28
b29: J1.79, X3.29
b30: J1.80, X3.30
b31: J1.81, X3.31
b32: J1.82, X3.32
b33: J1.83, X3.33
b34: J1.84, X3.34
b35: J1.85, X3.35
b36: J1.86, X3.36
b37: J1.87, X3.37
b38: J1.88, X3.38
b39: J1.89, X3.39
b40: J1.90, X3.40
b41: J1.91, X3.41
b42: J1.92, X3.42
b43: J1.93, X3.43
b44: J1.94, X3.44
b45: J1.95, X3.45
b46: J1.96, X3.46
b47: J1.97 (Pin_69), X3.47
b48: J1.98, X3.48
b49: J1.99, X3.49
b50: J1.100, X3.50
c01: J2.1, X5.1
c02: J2.2, X5.2
c03: J2.3, X5.3
c04: J2.4, X5.4
c05: J2.5, X5.5
c06: J2.6, X5.6
c07: J2.7, X5.7
c08: J2.8, X5.8
c09: J2.9, X5.9
c10: J2.10, X5.10
c11: J2.11, X5.11
c12: J2.12, X5.12
c13: J2.13, X5.13
c14: J2.14, X5.14
c15: J2.15, X5.15
c16: J2.16, X5.16
c17: J2.17, X5.17
c18: J2.18, X5.18
c19: J2.19, X5.19
c20: J2.20, X5.20
c21: J2.21, X5.21
c22: J2.22, X5.22
c23: J2.23, X5.23
c24: J2.24, X5.24
c25: J2.25, X5.25
c26: J2.26, X5.26
c27: J2.27, X5.27
c28: J2.28, X5.28
c29: J2.29, X5.29
c30: J2.30, X5.30
c31: J2.31, X5.31
c32: J2.32, X5.32
c33: J2.33, X5.33
c34: J2.34, X5.34
c35: J2.35, X5.35
c36: J2.36, X5.36
c37: J2.37, X5.37
c38: J2.38, X5.38
c39: J2.39, X5.39
c40: J2.40, X5.40
c41: J2.41, X5.41
c42: J2.42, X5.42
c43: J2.43, X5.43
c44: J2.44, X5.44
c45: J2.45, X5.45
c46: J2.46, X5.46
c47: J2.47, X5.47
c48: J2.48, X5.48
c49: J2.49, X5.49
c50: J2.50, X5.50
d01: J2.51, X7.1
d02: J2.52, X7.2
d03: J2.53, X7.3
d04: J2.54, X7.4
d05: J2.55, X7.5
d06: J2.56, X7.6
d07: J2.57, X7.7
d08: J2.58, X7.8
d09: J2.59, X7.9
d10: J2.60, X7.10
d11: J2.61, X7.11
d12: J2.62, X7.12
d13: J2.63, X7.13
d14: J2.64, X7.14
d15: J2.65, X7.15
d16: J2.66, X7.16
d17: J2.67, X7.17
d18: J2.68, X7.18
d19: J2.69, X7.19
d20: J2.70, X7.20
d21: J2.71, X7.21
d22: J2.72, X7.22
d23: J2.73, X7.23
d24: J2.74, X7.24
d25: J2.75, X7.25
d26: J2.76, X7.26
d27: J2.77, X7.27
d28: J2.78, X7.28
d29: J2.79, X7.29
d30: J2.80, X7.30
d31: J2.81, X7.31
d32: J2.82, X7.32
d33: J2.83, X7.33
d34: J2.84, X7.34
d35: J2.85, X7.35
d36: J2.86, X7.36
d37: J2.87, X7.37
d38: J2.88, X7.38
d39: J2.89, X7.39
d40: J2.90, X7.40
d41: J2.91, X7.41
d42: J2.92, X7.42
d43: J2.93, X7.43
d44: J2.94, X7.44
d45: J2.95, X7.45
d46: J2.96, X7.46
d47: J2.97 (Pin_69), X7.47
d48: J2.98, X7.48
d49: J2.99, X7.49
d50: J2.100, X7.50; also elsewhere on the board

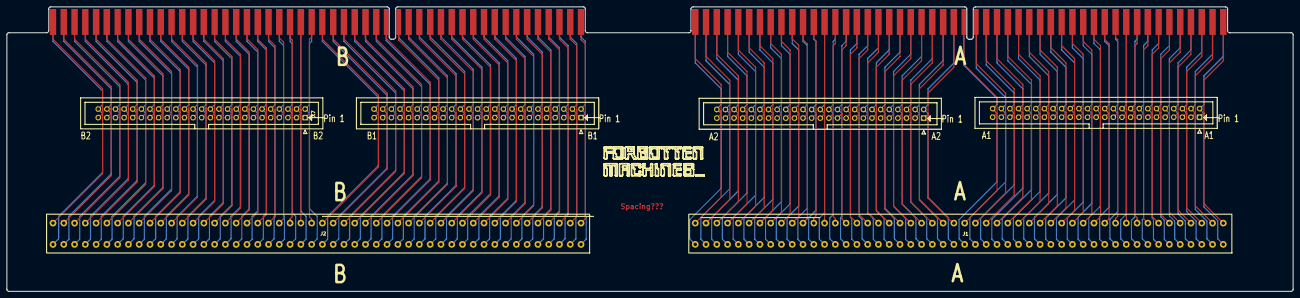
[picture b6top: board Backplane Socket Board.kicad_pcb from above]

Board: 2 copper layers, 379.0 x 83.8 mm, 8 parts (0 on the bottom side), 200 nets.

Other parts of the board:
J1#2: port A; portA_NovaMod
J2#2: port B; portB_NovaMod

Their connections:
d50: J2#2.100; also elsewhere on the board
